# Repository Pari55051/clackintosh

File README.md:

# Clackintosh
a wireless mechanical keyboard, with 75% layout (81 keys) and a rotary encoder. 
this accompanies my other hardware projects, namely, Clackinntosh Jr. (a macropad), Clackade (a small, very basic PCB-based game console), and Clickster (mouse based on Bambu Lab's Mouse Kit)

## Features
- 75% layout (81 keys) + a rotary encoder
- based on nice!nano v2 MCU
- has underglow LEDs to light up the side-printed keycaps
- hotswappable switches (Cherry MX Red/Brown)
- wireless with 10000mah battery
- ~ 4° tilt for ergonomics
- ZMK firmware
- a blank white case to put some stickers on it!
- an accompanying wristrest

## Images

## General

> not the assembled version, i'm hoping for it to look like this with the keycap set

### Schematic

### PCB

> this would have hotswappable switches, i did not add t to the pcb since i had to manually add for each key, the footprint is chosen appropriately

### Case
> the case has space on top to add custom stickers (hackclub merch ones, since i don't know where to put them)

### Full Assembly
> the fully assembled one's PCB is not placed properly (not rotated to the correct angle) since there was some unknwon error in onshape where i could not rotate the thing, whenever i tried to rotate it would load and then no changes would occur. i tried my best to rotate it, and debug this but could not do so.
> will update the images if i'm able to do so in the future

## Challenges
the biggest challenge i faced was getting the schematcs right. i got the thing reviewed multiple times (on reddit, on #highway), added components, removed components, re-added components (capacitors, i'm looking at you)
another challenge was the case CAD, which had unexpected errors.

## BOM
|S. | Item | Quantity | Price | Link | Notes|
|---|------|----------|-------|------|------|
|1.| Case (incl. wristrest) | 1 | - | - | printed though printing legion|
|2.| Knob for rotary encoder | 1 | - | - | printed though printing legion |
|3.| Switches - Akko V3 Cream Black Pro | 81 | Rs.2398 ($27.41) | [StacksKB](https://stackskb.com/store/akko-v3-cream-black-pro-switch-pack-of-45/) | ordered two since it is a packof 48, free shipping |
|4.| Hotswappable Sockets | 81 | Rs.1090 ($12.46) [incl. shipping of about $1.14] | [Neo Macro](https://neomacro.in/products/kailh-mx-hotswap-socket?variant=49467139227926) | 9 qty. ordered, since it is a set of 10 |
|5.| Stabilizers | 3 (2u) + 1 (6.5u) | Rs.1585 ($18.12) | [StacksKB](https://stackskb.com/store/durock-smokey-screw-in-stabilizers-v2/) | no shipping  charge |
|6.| Rotary Encoder - EC11 | 1 | Rs.172 ($1.97) | [Amazon.in](https://www.amazon.in/CentIoT-Encoder-Digital-Potentiometer-Control/dp/B0888RWNM1?crid=3H3ISLY2V9ZH5&dib=eyJ2IjoiMSJ9.ub-gVfIJkebgtPjQTQbP-1BNXrl39Ma9zP8YixnEs_uWGd82NzxokakbTgGlfXwvvbwKo1NhVn8iubL8tae9Wi_LafgLePaeA8Y5kPpV_qPI44pqsRB9mX7KN7ImQM3n8NkbTE3-eBYAXxmhAxua2NCHESNwFMZotrqkj7qS_SXR2kNxvQyZ_2nftByqA3GmRFQRc5_pbxpjeeLxiwJslTPwFi5ZTk4HPx0DrsHFBGxiNN7eGaSqn3sTKCzVceu6slag52Omg1vD_geqB3qQy1fCUWTE4n0WXS43WMdFLFM.jLY7U2FxXnWHCqS6s6jF70LCJ59HVkYHE3qNwtnKg8c&dib_tag=se&keywords=ec11+rotary+encoder&qid=1753984957&sprefix=ec1+rotary+encoder,aps,248&sr=8-3) | - |
|7.| Keycaps Set - side printed blue | 1 | Rs.1299 ($14.85) | [StacksKB](https://stackskb.com/store/veekos-gradient-keycaps-cherry-profile-135-keys/) | - |
|8.| Nice!Nano v2 --> Pro Micro | 1 | Rs.758 ($8.66) [incl. $1.13 shipping] | [Probots](https://probots.co.in/pro-micro-nrf52840-development-board-compatible-with-nice-nano-v2-0.html) | compatible with nice!nano, and wayy cheaper |
|9.| SK6812Mini-E neopixels | 20 | Rs.752.23 ($8.60) [incl. $3.74 shipping] | [LCSC](https://lcsc.com/product-detail/RGB-LEDs-Built-in-IC_OPSCO-Optoelectronics-SK6812MINI-E_C5149201.html) | for underglow for keycap visibility, not available anywhere else |
|10.| 100nF Capacitors | 21 | Rs.210 ($2.40) | [Amazon.in](https://www.amazon.in/100pcs-Ceramic-disc-Capacitor-100nf/dp/B08FB2NZ1L?crid=1P652WXADOQHF&dib=eyJ2IjoiMSJ9.E6nRIu5_9YSDNISKzn4qatrWKc7EAydC5mq-F6L7MHSy5aPsfXFMTJ5_YvUvcr9VMIJbHGUdi3eBkWF5oDmjaacjcfmvGjy_XeRrO_PjSvponr2Hf7R18_c3LzMLQi0FFVdox1j2iH-b0jLGImJp5rD-2L-z6mJmC7ETmGFaMeO5tWXr0HIAFSVg7xGD-4CcUEqQRS0xvEK06J5SDaOMluZfmk0X8pTOrxUoOlBwLcA.CWHiOOZnuk92qXruggDfBMzOhlwUS12HJFRN06HVaMo&dib_tag=se&keywords=100nf+50v+capacitor&qid=1753986573&sprefix=100nf+50v+capacitor,aps,259&sr=8-1) | decoupling + used in i2c expander |
|11.| I2C Expander - MCP23017 | 1 | Rs.258.99 ($2.96) | [RoboticsDNA](https://roboticsdna.in/product/mcp23017-e-sp-microchip-i-o-expander-16-bit-i2c-serial-1-8-v-5-5-v-dip-28-pins/) | short on GPIOs, had to use it |
|12.| Resitors - 4.7k ohm | 2 | Rs.9 ($0.10) | [Robocraze](https://robocraze.com/products/4-7k-resistor-pack-of-10?_psq=4.7k&_v=1.0) | pullups for i2c|
|13.| Diodes - 1N4148 though-hole | 81 | Rs.135 ($1.54) | [StacksKB](https://stackskb.com/store/1n4148-through-hole-diode/) | - |
|14.| 100000mah Battery | 1 | Rs.667 ($7.62) | [Amazon.in](https://www.amazon.in/Portronics-Luxcell-Charging-Output-Button/dp/B0CQK537RQ?crid=30FNXN02G1VQR&dib=eyJ2IjoiMSJ9.SeZBu50Z5maKPBAPuVGIZaCCnuOaK6YIpKFiUoF4lZQMYfVNpBJboLyC4tyXAsvwRIplSp-oxbmFdRZWTLahpCL1Q4RiwgB4HW9QNR0LmMgB_EUeq1E8ImJ_e7xXOxy0p5tsyDBqRuEUn6Z59A_S5TXZKBqEuU-zjyu8vzbfmJr2ysZdim2Oi61aNqKcXVYLygXPOqpGwnpAPvTcgXFo3tB0ZWwji8zyMWBCC2CIGC0.OQO0LtasTF-RZUJpMsytapOf96OHgtbrssq44zcfY8s&dib_tag=se&keywords=10000+mah+battery&qid=1753991573&sprefix=10000mag+battery,aps,203&sr=8-14&th=1) | for long battery life, using this since this is wayy cheaper then the li-po battery |
|15.| M3x12mm screws | 4 | Rs.159 ($1.82) | [Amazon.in](https://www.amazon.in/gp/product/B07XY78Q73?smid=A1QGCD9W0FP1ZA&th=1) | to assemble the case |
|16.| M3x5mm heatset inserts | 4 | Rs.170 ($1.94) | [Amazon.in](https://www.amazon.in/gp/product/B0CX1BS7DJ?smid=A1QGCD9W0FP1ZA&psc=1) | to assemble the case |
|17.| Slide Switch (SPDT) | 1 | Rs.14 ($0.16) | [Robocraze](https://robocraze.com/products/slide-switch-3-pin-2-way-spdt?_psq=spdt&_v=1.0) | to turn the keeb on/off |
|18.| PCB | 5 (default via jlcpcb) | Rs.2780.57 ($31.78) | - | - | 

**TOTAL AMOUNT = Rs.12,457.79 ($142.39) [excl. shipping for printing legion]**

## Credits

- made by: [unowen](https://github.com/pari55051)
- inspiration: some image i found on google
- schem: shout out to all the people who helped me fixed the thing
- case: shout out to "One For Freedom" for helping resolve errors in the cad
- canva: for base version of the logo, which i had to edit later in figma
- StacksKB: "final look" image from website

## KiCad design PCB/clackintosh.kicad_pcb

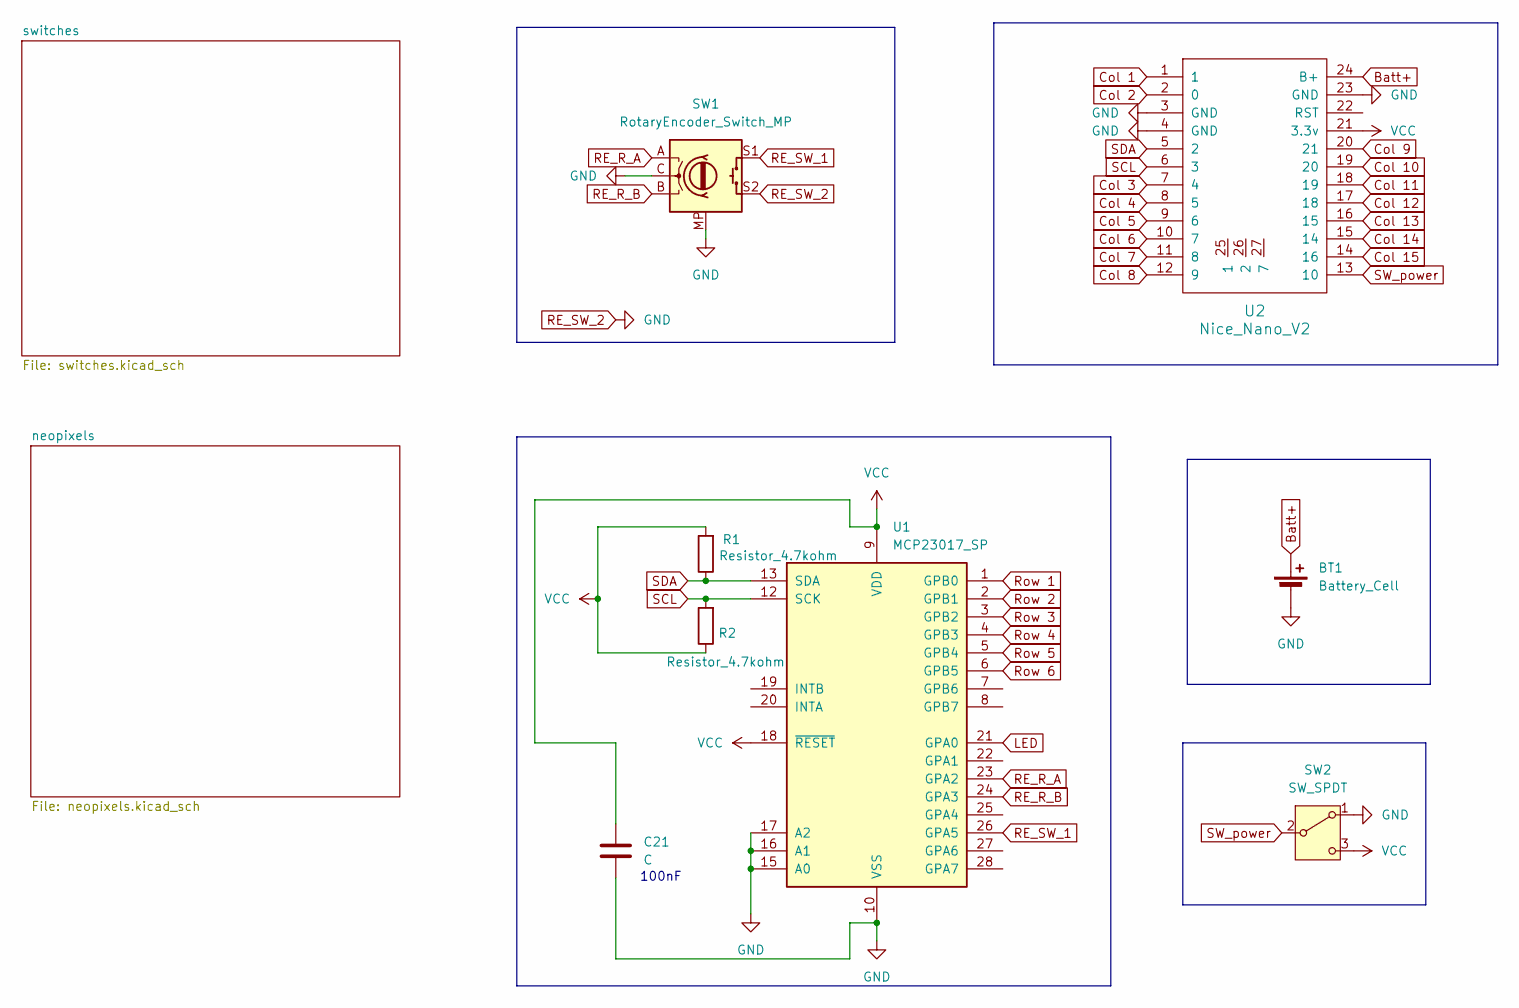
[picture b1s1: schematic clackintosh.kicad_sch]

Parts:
BT1: Battery_Cell; Battery
C21: C; CP_Radial_D5.0mm_P2.50mm
R1, R2: Resistor_4.7kohm; R_Axial_DIN0207_L6.3mm_D2.5mm_P7.62mm_Horizontal
SW1: RotaryEncoder_Switch_MP; RotaryEncoder_Alps_EC11E-Switch_Vertical_H20mm
SW2: SW_SPDT; SW_MINI-SPDT-SW
U1: MCP23017_SP; DIP-28_W7.62mm
U2: Nice_Nano_V2

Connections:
Batt+: BT1.1 (+), U2.24 (B+)
Col 1: U2.1; also elsewhere on the board
Col 2: U2.2 (0); also elsewhere on the board
Col 3: U2.7 (4); also elsewhere on the board
Col 4: U2.8 (5); also elsewhere on the board
Col 5: U2.9 (6); also elsewhere on the board
Col 6: U2.10 (7); also elsewhere on the board
Col 7: U2.11 (8); also elsewhere on the board
Col 8: U2.12 (9); also elsewhere on the board
Col 9: U2.20 (21); also elsewhere on the board
Col 10: U2.19 (20); also elsewhere on the board
Col 11: U2.18 (19); also elsewhere on the board
Col 12: U2.17 (18); also elsewhere on the board
Col 13: U2.16 (15); also elsewhere on the board
Col 14: U2.15 (14); also elsewhere on the board
Col 15: U2.14 (16); also elsewhere on the board
LED: U1.21 (GPA0); also elsewhere on the board
RE_R_A: SW1.A, U1.23 (GPA2)
RE_R_B: SW1.B, U1.24 (GPA3)
RE_SW_1: SW1.S1, U1.26 (GPA5)
RE_SW_2: BT1.2 (-), C21.2, SW1.C, SW1.MP, SW1.S2, SW2.1 (A), U1.10 (VSS), U1.15 (A0), U1.16 (A1), U1.17 (A2), U2.3 (GND), U2.4 (GND), U2.23 (GND); also elsewhere on the board
Row 1: U1.1 (GPB0); also elsewhere on the board
Row 2: U1.2 (GPB1); also elsewhere on the board
Row 3: U1.3 (GPB2); also elsewhere on the board
Row 4: U1.4 (GPB3); also elsewhere on the board
Row 5: U1.5 (GPB4); also elsewhere on the board
Row 6: U1.6 (GPB5); also elsewhere on the board
SCL: R2.2, U1.12 (SCK), U2.6 (3)
SDA: R1.1, U1.13 (SDA), U2.5 (2)
SW_power: SW2.2 (B), U2.13 (10)
VCC: C21.1, R1.2, R2.1, SW2.3 (C), U1.9 (VDD), U1.18 (~RESET), U2.21 (3.3v); also elsewhere on the board

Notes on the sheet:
100nF

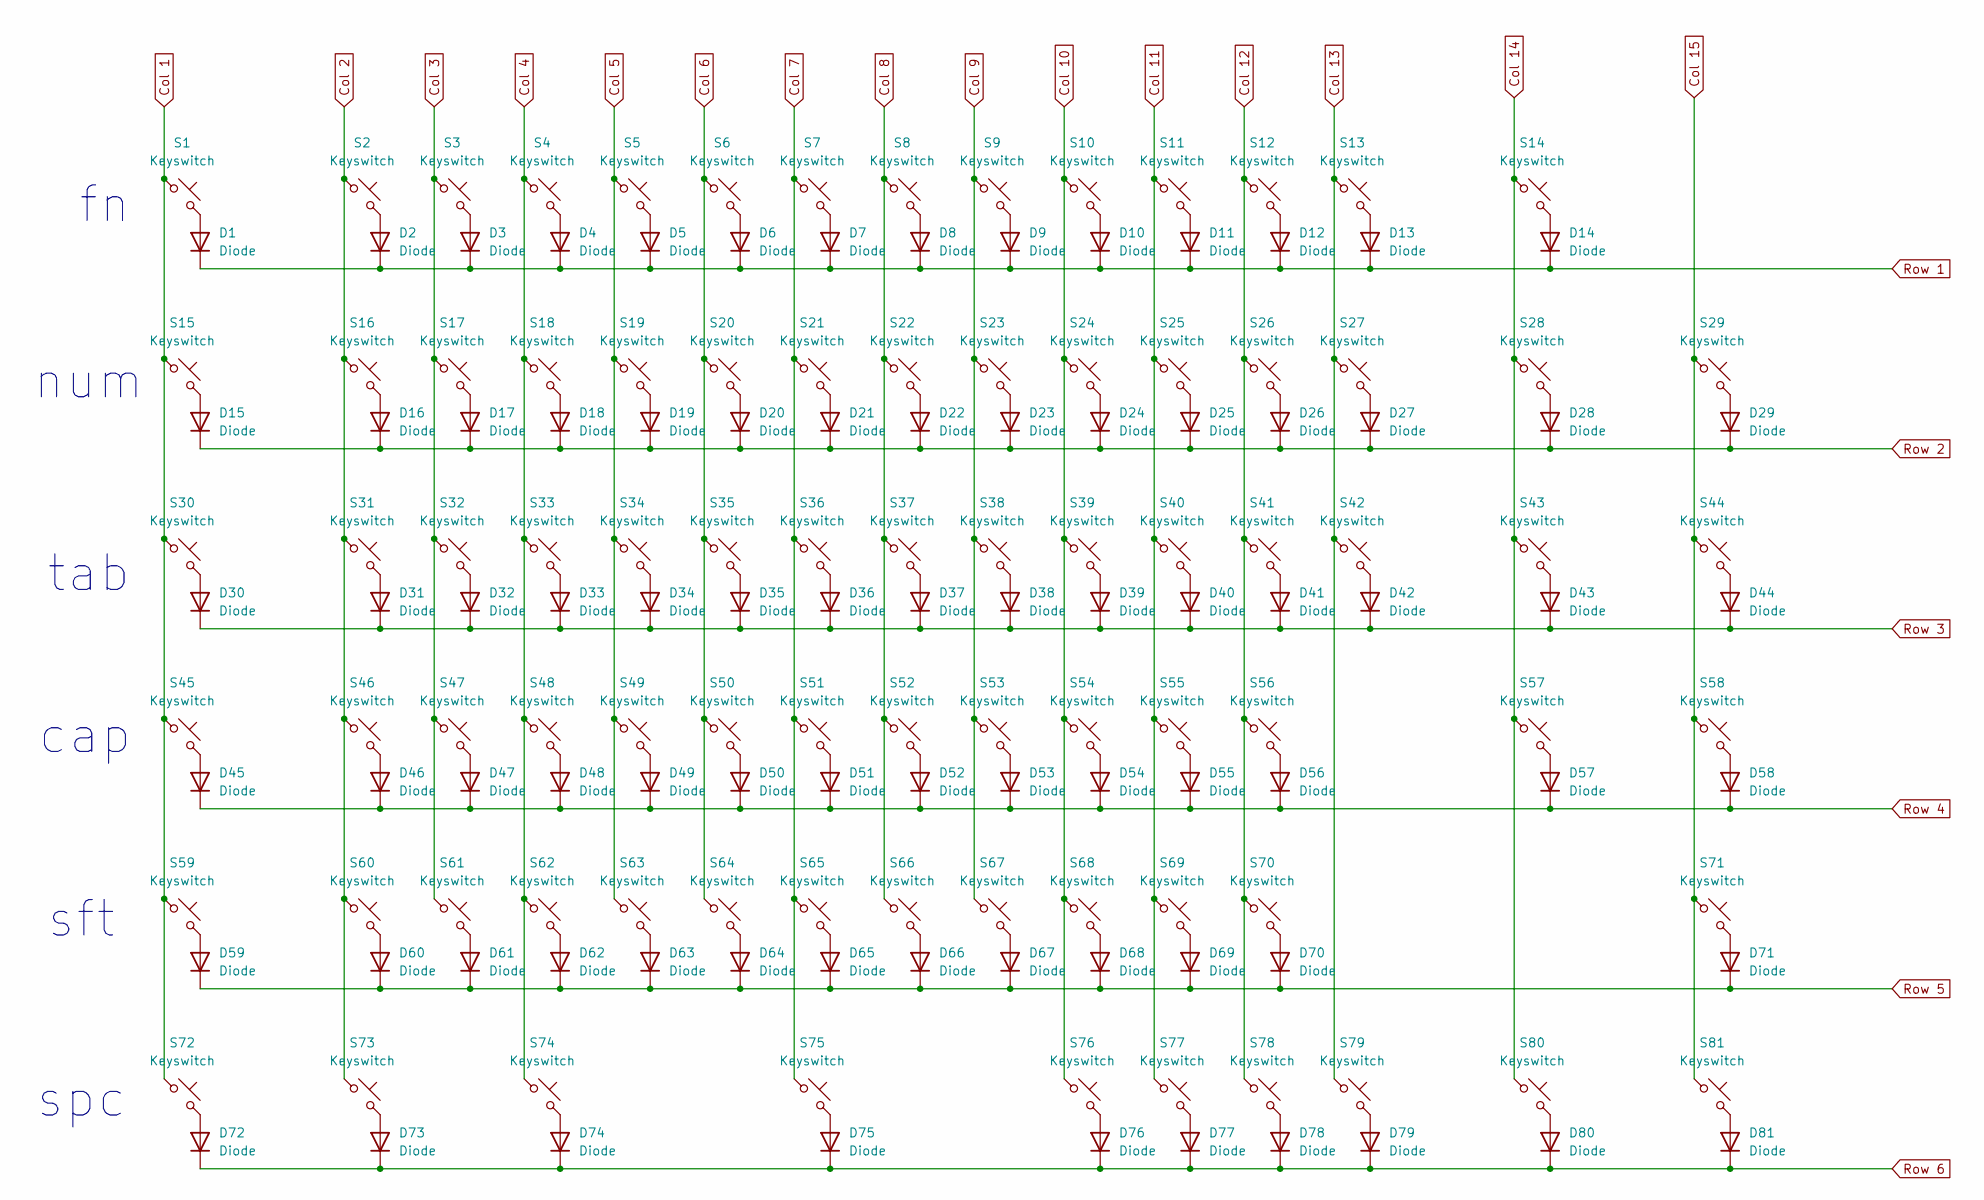
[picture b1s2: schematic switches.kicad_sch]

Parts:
D1, D2, D3, D4, D5, D6, D7, D8, D9, D10, D11, D12, D13, D14, D15, D16, D17, D18, D19, D20, D21, D22, D23, D24, D25, D26, D27, D28, D29, D30, D31, D32, D33, D34, D35, D36, D37, D38, D39, D40, D41, D42, D43, D44, D45, D46, D47, D48, D49, D50, D51, D52, D53, D54, D55, D56, D57, D58, D59, D60, D61, D62, D63, D64, D65, D66, D67, D68, D69, D70, D71, D72, D73, D74, D75, D76, D77, D78, D79, D80, D81: Diode; D_DO-35_SOD27_P7.62mm_Horizontal
S1, S2, S3, S4, S5, S6, S7, S8, S9, S10, S11, S12, S13, S14, S15, S16, S17, S18, S19, S20, S21, S22, S23, S24, S25, S26, S27, S29, S31, S32, S33, S34, S35, S36, S37, S38, S39, S40, S41, S42, S44, S46, S47, S48, S49, S50, S51, S52, S53, S54, S55, S56, S58, S60, S61, S62, S63, S64, S65, S66, S67, S68, S69, S70, S71, S73, S76, S77, S78, S79, S80, S81: Keyswitch; MX_Hotswap_1.00u
S28: Keyswitch; MX_Hotswap_2.00u
S30, S43: Keyswitch; MX_Hotswap_1.50u
S45: Keyswitch; MX_Hotswap_1.75u
S57, S59: Keyswitch; MX_Hotswap_2.25u
S72, S74: Keyswitch; MX_Hotswap_1.25u
S75: Keyswitch; MX_Hotswap_6.25u

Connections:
Col 1: S1.1, S15.1, S30.1, S45.1, S59.1, S72.1; also elsewhere on the board
Col 2: S2.1, S16.1, S31.1, S46.1, S60.1, S73.1; also elsewhere on the board
Col 3: S3.1, S17.1, S32.1, S47.1, S61.1; also elsewhere on the board
Col 4: S4.1, S18.1, S33.1, S48.1, S62.1, S74.1; also elsewhere on the board
Col 5: S5.1, S19.1, S34.1, S49.1, S63.1; also elsewhere on the board
Col 6: S6.1, S20.1, S35.1, S50.1, S64.1; also elsewhere on the board
Col 7: S7.1, S21.1, S36.1, S51.1, S65.1, S75.1; also elsewhere on the board
Col 8: S8.1, S22.1, S37.1, S52.1, S66.1; also elsewhere on the board
Col 9: S9.1, S23.1, S38.1, S53.1, S67.1; also elsewhere on the board
Col 10: S10.1, S24.1, S39.1, S54.1, S68.1, S76.1; also elsewhere on the board
Col 11: S11.1, S25.1, S40.1, S55.1, S69.1, S77.1; also elsewhere on the board
Col 12: S12.1, S26.1, S41.1, S56.1, S70.1, S78.1; also elsewhere on the board
Col 13: S13.1, S27.1, S42.1, S79.1; also elsewhere on the board
Col 14: S14.1, S28.1, S43.1, S57.1, S80.1; also elsewhere on the board
Col 15: S29.1, S44.1, S58.1, S71.1, S81.1; also elsewhere on the board
unnamed: D1.2 (A), S1.2
unnamed: D2.2 (A), S2.2
unnamed: D3.2 (A), S3.2
unnamed: D4.2 (A), S4.2
unnamed: D5.2 (A), S5.2
unnamed: D6.2 (A), S6.2
unnamed: D7.2 (A), S7.2
unnamed: D8.2 (A), S8.2
unnamed: D9.2 (A), S9.2
unnamed: D10.2 (A), S10.2
unnamed: D11.2 (A), S11.2
unnamed: D12.2 (A), S12.2
unnamed: D13.2 (A), S13.2
unnamed: D14.2 (A), S14.2
unnamed: D15.2 (A), S15.2
unnamed: D16.2 (A), S16.2
unnamed: D17.2 (A), S17.2
unnamed: D18.2 (A), S18.2
unnamed: D19.2 (A), S19.2
unnamed: D20.2 (A), S20.2
unnamed: D21.2 (A), S21.2
unnamed: D22.2 (A), S22.2
unnamed: D23.2 (A), S23.2
unnamed: D24.2 (A), S24.2
unnamed: D25.2 (A), S25.2
unnamed: D26.2 (A), S26.2
unnamed: D27.2 (A), S27.2
unnamed: D28.2 (A), S28.2
unnamed: D29.2 (A), S29.2
unnamed: D30.2 (A), S30.2
unnamed: D31.2 (A), S31.2
unnamed: D32.2 (A), S32.2
unnamed: D33.2 (A), S33.2
unnamed: D34.2 (A), S34.2
unnamed: D35.2 (A), S35.2
unnamed: D36.2 (A), S36.2
unnamed: D37.2 (A), S37.2
unnamed: D38.2 (A), S38.2
unnamed: D39.2 (A), S39.2
unnamed: D40.2 (A), S40.2
unnamed: D41.2 (A), S41.2
unnamed: D42.2 (A), S42.2
unnamed: D43.2 (A), S43.2
unnamed: D44.2 (A), S44.2
unnamed: D45.2 (A), S45.2
unnamed: D46.2 (A), S46.2
unnamed: D47.2 (A), S47.2
unnamed: D48.2 (A), S48.2
unnamed: D49.2 (A), S49.2
unnamed: D50.2 (A), S50.2
unnamed: D51.2 (A), S51.2
unnamed: D52.2 (A), S52.2
unnamed: D53.2 (A), S53.2
unnamed: D54.2 (A), S54.2
unnamed: D55.2 (A), S55.2
unnamed: D56.2 (A), S56.2
unnamed: D57.2 (A), S57.2
unnamed: D58.2 (A), S58.2
unnamed: D59.2 (A), S59.2
unnamed: D60.2 (A), S60.2
unnamed: D61.2 (A), S61.2
unnamed: D62.2 (A), S62.2
unnamed: D63.2 (A), S63.2
unnamed: D64.2 (A), S64.2
unnamed: D65.2 (A), S65.2
unnamed: D66.2 (A), S66.2
unnamed: D67.2 (A), S67.2
unnamed: D68.2 (A), S68.2
unnamed: D69.2 (A), S69.2
unnamed: D70.2 (A), S70.2
unnamed: D71.2 (A), S71.2
unnamed: D72.2 (A), S72.2
unnamed: D73.2 (A), S73.2
unnamed: D74.2 (A), S74.2
unnamed: D75.2 (A), S75.2
unnamed: D76.2 (A), S76.2
unnamed: D77.2 (A), S77.2
unnamed: D78.2 (A), S78.2
unnamed: D79.2 (A), S79.2
unnamed: D80.2 (A), S80.2
unnamed: D81.2 (A), S81.2
Row 1: D1.1 (K), D2.1 (K), D3.1 (K), D4.1 (K), D5.1 (K), D6.1 (K), D7.1 (K), D8.1 (K), D9.1 (K), D10.1 (K), D11.1 (K), D12.1 (K), D13.1 (K), D14.1 (K); also elsewhere on the board
Row 2: D15.1 (K), D16.1 (K), D17.1 (K), D18.1 (K), D19.1 (K), D20.1 (K), D21.1 (K), D22.1 (K), D23.1 (K), D24.1 (K), D25.1 (K), D26.1 (K), D27.1 (K), D28.1 (K), D29.1 (K); also elsewhere on the board
Row 3: D30.1 (K), D31.1 (K), D32.1 (K), D33.1 (K), D34.1 (K), D35.1 (K), D36.1 (K), D37.1 (K), D38.1 (K), D39.1 (K), D40.1 (K), D41.1 (K), D42.1 (K), D43.1 (K), D44.1 (K); also elsewhere on the board
Row 4: D45.1 (K), D46.1 (K), D47.1 (K), D48.1 (K), D49.1 (K), D50.1 (K), D51.1 (K), D52.1 (K), D53.1 (K), D54.1 (K), D55.1 (K), D56.1 (K), D57.1 (K), D58.1 (K); also elsewhere on the board
Row 5: D59.1 (K), D60.1 (K), D61.1 (K), D62.1 (K), D63.1 (K), D64.1 (K), D65.1 (K), D66.1 (K), D67.1 (K), D68.1 (K), D69.1 (K), D70.1 (K), D71.1 (K); also elsewhere on the board
Row 6: D72.1 (K), D73.1 (K), D74.1 (K), D75.1 (K), D76.1 (K), D77.1 (K), D78.1 (K), D79.1 (K), D80.1 (K), D81.1 (K); also elsewhere on the board

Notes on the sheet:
tab
num
sft
cap
spc

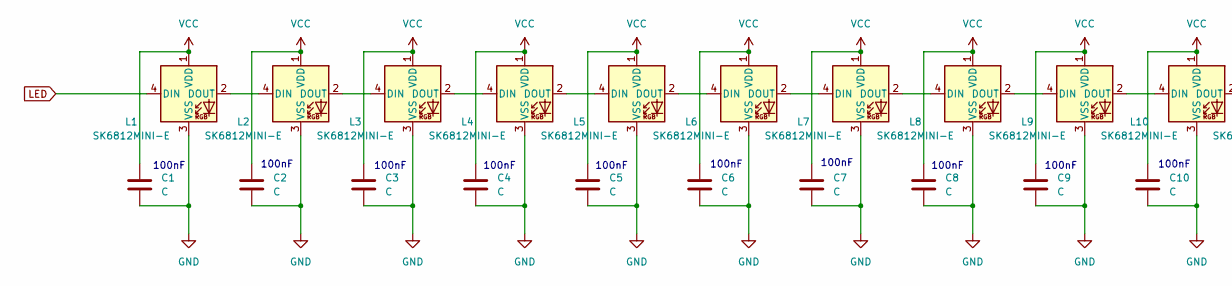
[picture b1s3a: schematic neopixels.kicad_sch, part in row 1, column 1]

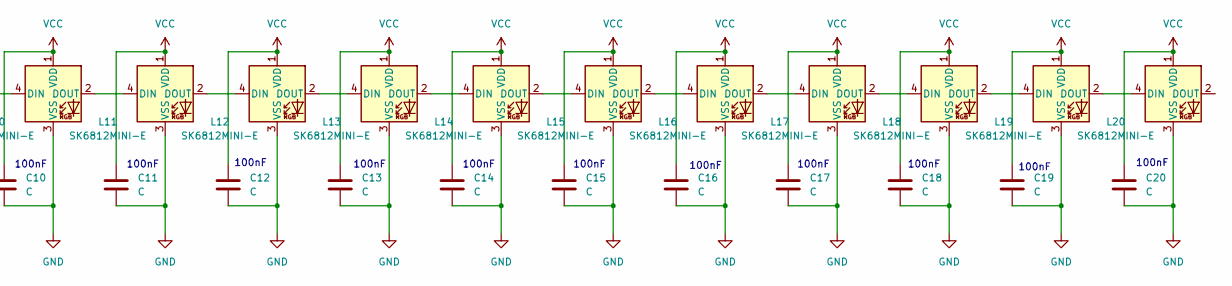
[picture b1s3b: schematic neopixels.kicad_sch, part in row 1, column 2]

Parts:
C1, C2, C3, C4, C5, C6, C7, C8, C9, C10, C11, C12, C13, C14, C15, C16, C17, C18, C19, C20: C; CP_Radial_D5.0mm_P2.50mm
L1, L2, L3, L4, L5, L6, L7, L8, L9, L10, L11, L12, L13, L14, L15, L16, L17, L18, L19, L20: SK6812MINI-E; MX SK6812MINI E (1)

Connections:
LED: L1.4 (DIN); also elsewhere on the board
unnamed: L1.2 (DOUT), L2.4 (DIN)
unnamed: L2.2 (DOUT), L3.4 (DIN)
unnamed: L3.2 (DOUT), L4.4 (DIN)
unnamed: L4.2 (DOUT), L5.4 (DIN)
unnamed: L5.2 (DOUT), L6.4 (DIN)
unnamed: L6.2 (DOUT), L7.4 (DIN)
unnamed: L7.2 (DOUT), L8.4 (DIN)
unnamed: L8.2 (DOUT), L9.4 (DIN)
unnamed: L9.2 (DOUT), L10.4 (DIN)
unnamed: L10.2 (DOUT), L11.4 (DIN)
unnamed: L11.2 (DOUT), L12.4 (DIN)
unnamed: L12.2 (DOUT), L13.4 (DIN)
unnamed: L13.2 (DOUT), L14.4 (DIN)
unnamed: L14.2 (DOUT), L15.4 (DIN)
unnamed: L15.2 (DOUT), L16.4 (DIN)
unnamed: L16.2 (DOUT), L17.4 (DIN)
unnamed: L17.2 (DOUT), L18.4 (DIN)
unnamed: L18.2 (DOUT), L19.4 (DIN)
unnamed: L19.2 (DOUT), L20.4 (DIN)
RE_SW_2: C1.2, C2.2, C3.2, C4.2, C5.2, C6.2, C7.2, C8.2, C9.2, C10.2, C11.2, C12.2, C13.2, C14.2, C15.2, C16.2, C17.2, C18.2, C19.2, C20.2, L1.3 (VSS), L2.3 (VSS), L3.3 (VSS), L4.3 (VSS), L5.3 (VSS), L6.3 (VSS), L7.3 (VSS), L8.3 (VSS), L9.3 (VSS), L10.3 (VSS), L11.3 (VSS), L12.3 (VSS), L13.3 (VSS), L14.3 (VSS), L15.3 (VSS), L16.3 (VSS), L17.3 (VSS), L18.3 (VSS), L19.3 (VSS), L20.3 (VSS); also elsewhere on the board
VCC: C1.1, C2.1, C3.1, C4.1, C5.1, C6.1, C7.1, C8.1, C9.1, C10.1, C11.1, C12.1, C13.1, C14.1, C15.1, C16.1, C17.1, C18.1, C19.1, C20.1, L1.1 (VDD), L2.1 (VDD), L3.1 (VDD), L4.1 (VDD), L5.1 (VDD), L6.1 (VDD), L7.1 (VDD), L8.1 (VDD), L9.1 (VDD), L10.1 (VDD), L11.1 (VDD), L12.1 (VDD), L13.1 (VDD), L14.1 (VDD), L15.1 (VDD), L16.1 (VDD), L17.1 (VDD), L18.1 (VDD), L19.1 (VDD), L20.1 (VDD); also elsewhere on the board

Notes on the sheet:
100nF

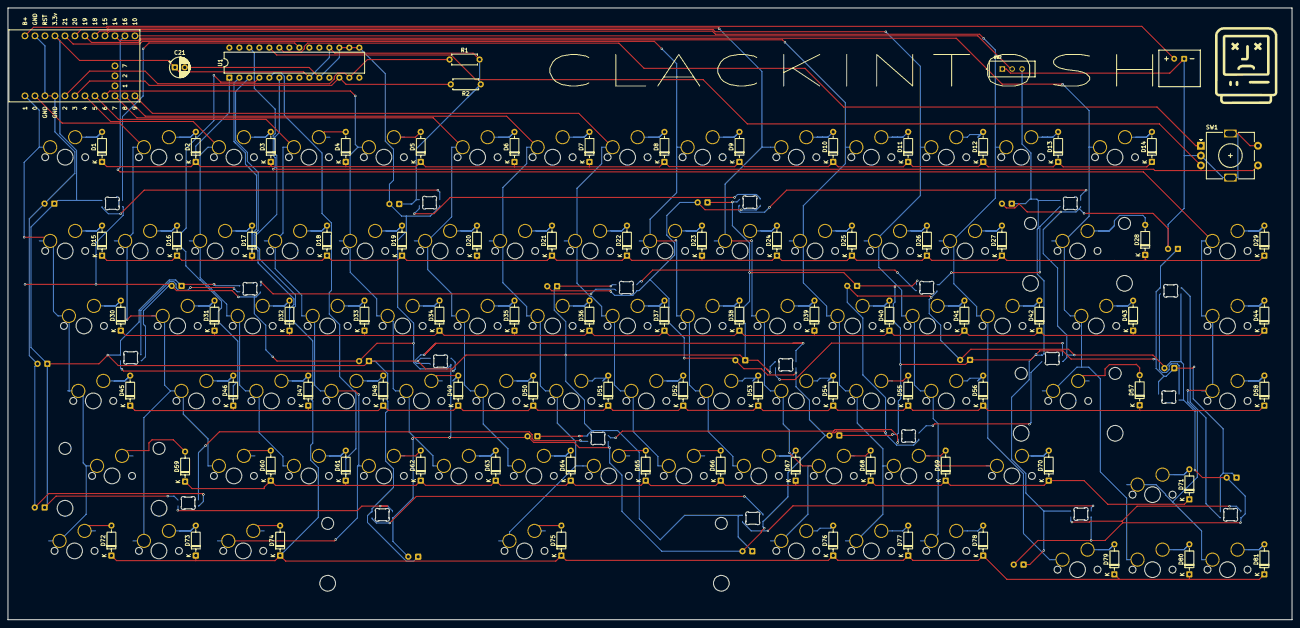
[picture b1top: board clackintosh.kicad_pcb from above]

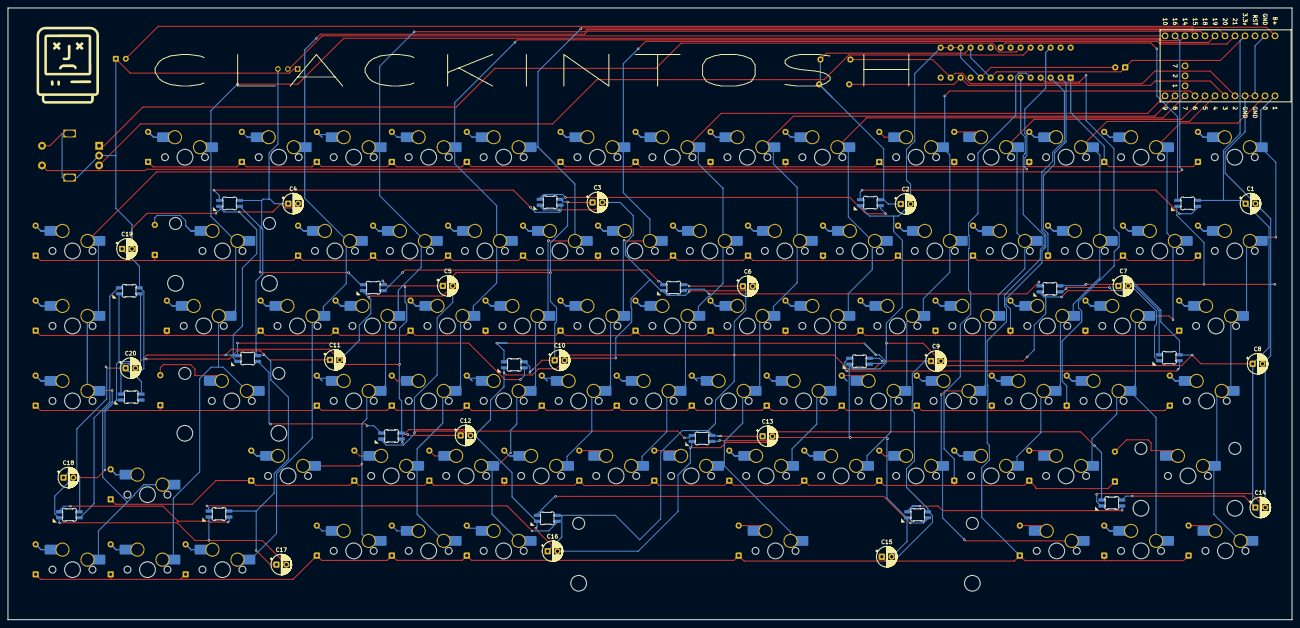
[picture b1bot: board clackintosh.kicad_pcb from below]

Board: 2 copper layers, 326.2 x 155.4 mm, 210 parts (101 on the bottom side), 131 nets.

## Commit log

2025-07-30 initial version keeb pcb files
2025-07-31 final files
2025-08-01 after-review updates
